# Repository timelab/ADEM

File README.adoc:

= Timelab ADEM project

image::https://api.travis-ci.org/timelab/ADEM.svg[alt="Build Status", link="https://travis-ci.org/timelab/ADEM", align="left", float]

The http://www.timelab.org/[Timelab] ADEM project enables cyclists to measure particulate matter (PM~1~ and PM~2.5~). The air quality estimate based on these measurements is displayed on the device, temporarily stored and sent via WiFi to a central data collection service.

The aim of this project is to create a low-cost open-source DIY hardware and firmware kit that is modular and adjustable, can be locally reproduced and repaired.

This git repository hosts the hardware designs, firmware and technical documentation for the ADEM device. You can find the documentation at: https://github.com/timelab/ADEM/tree/master/docs[]

More information related to this project is available from the project's wiki at: http://wiki.timelab.org/wiki/A.D.E.M[]

We welcome feedback and contributions.

image::http://timelab.github.io/ADEM-Logos/svg/adem_logo-txt_stroke.svg[alt="ADEM logo", link="http://ik-adem.be/", align="right", float]

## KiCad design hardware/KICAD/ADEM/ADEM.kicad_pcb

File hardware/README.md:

# Hardware

The project uses the SparkFun Thing. This ESP8266 based Wi-Fi controller development board runs the A.D.E.M. firmware and conveniently hosts a LiPo battery management system that is key in the mobility aspect of this project. Apart from the headers for the SparkFun Thing, the project's printed circuit board has room for a GPS module, temperature and pressure sensors and connections to external parts like the PPD40NS dust sensor.

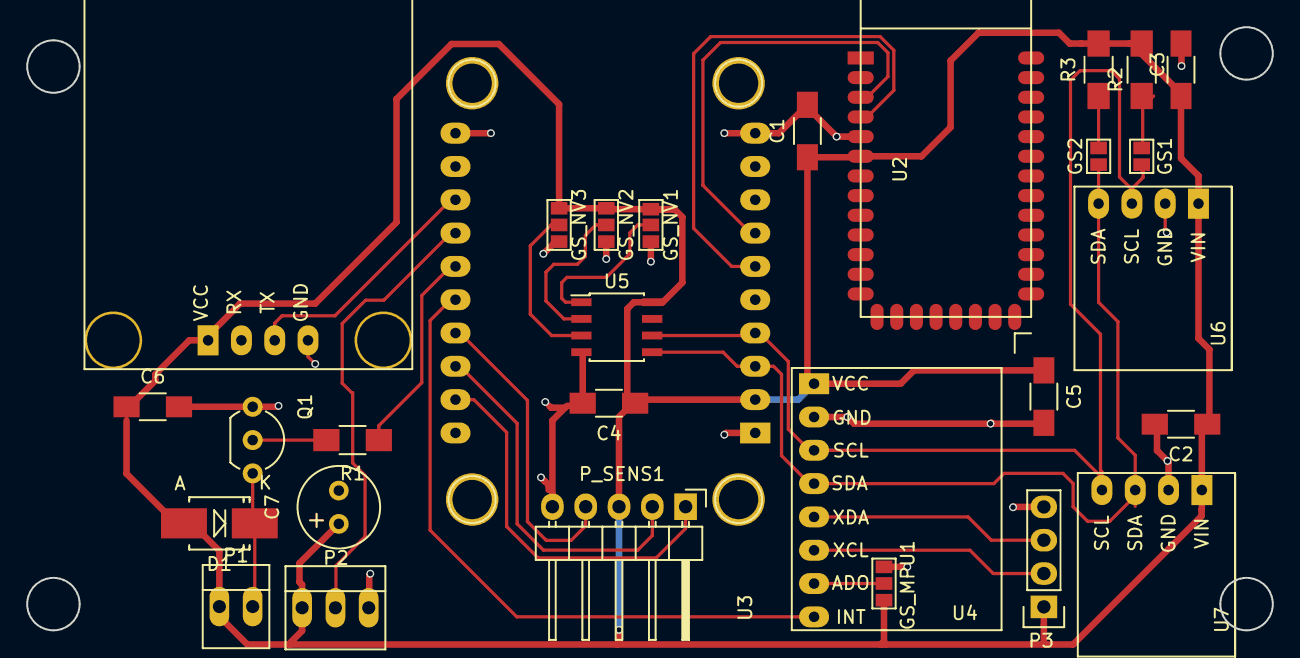
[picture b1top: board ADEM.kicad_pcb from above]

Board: 2 copper layers, 95.0 x 46.0 mm, 29 parts (0 on the bottom side), 23 nets.

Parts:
C1, C2, C3, C4, C5, C6: C; C_1206_HandSoldering
C7: CP; Elko_vert_11.2x6.3mm_RM2.5
D1: DIODE; SMB_Handsoldering
GS1: GS1; GS2
GS2: GS2
GS_MPU1: GS_A0; GS3
GS_NV1: GS_A0; GS3
GS_NV2: GS_A1; GS3
GS_NV3: GS_A2; GS3
P1: CONN_buzz; PINHEAD1-2
P2: CONN_01X03; PINHEAD1-3
P3: CONN_01X04; Pin_Header_Straight_1x04
P_SENS1: CONN_01X05; Pin_Header_Angled_1x05
Q1: NPN; TO-92_Inline_Wide
R1, R2, R3: R; R_1206_HandSoldering
U1: GY-NEO6MV2
U2: HC05; HC-05
U3: ESP8266_THING
U4: MPU6050
U5: NVSRAM; SOIC-8_3.9x4.9mm_Pitch1.27mm
U6: BMP180
U7: HTU21D

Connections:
A_SENSOR: P_SENS1.1, U3.19
BT_RX: U2.4, U3.6
BT_TX: U2.3, U3.7
BUZZ: R1.1, U3.15
GND: C1.2, C2.2, C3.2, C4.2, C5.2, C6.2, C7.2, GS_MPU1.3, GS_NV1.3, GS_NV2.3, GS_NV3.3, P2.3, P3.4, P_SENS1.5, Q1.1, U1.4, U2.5, U3.1, U3.10, U3.11, U4.2, U5.4, U6.2, U7.2
GPS_RX: U1.3, U3.13
INT: U3.16, U4.8
NEO_PXL: P2.2, U3.14
unnamed: D1.1, P1.2, Q1.3
unnamed: GS1.1, R2.2
unnamed: GS2.2, R3.1
unnamed: GS_MPU1.2, U4.7
unnamed: GS_NV1.2, U5.1
unnamed: GS_NV2.2, U5.2
unnamed: GS_NV3.2, U5.3
unnamed: P3.2, U4.6
unnamed: P3.3, U4.5
unnamed: Q1.2, R1.2
P10_SENS: P_SENS1.2, U3.18
P25_SENS: P_SENS1.4, U3.17
SCL: GS1.2, U3.4, U4.3, U5.6, U6.3, U7.4
SDA: GS2.1, U3.3, U4.4, U5.5, U6.4, U7.3
VCC: C1.1, C2.1, C3.1, C4.1, C5.1, C6.1, C7.1, D1.2, GS_MPU1.1, GS_NV1.1, GS_NV2.1, GS_NV3.1, P1.1, P2.1, P3.1, P_SENS1.3, R2.1, R3.2, U1.1, U2.6, U3.2, U4.1, U5.8, U6.1, U7.1

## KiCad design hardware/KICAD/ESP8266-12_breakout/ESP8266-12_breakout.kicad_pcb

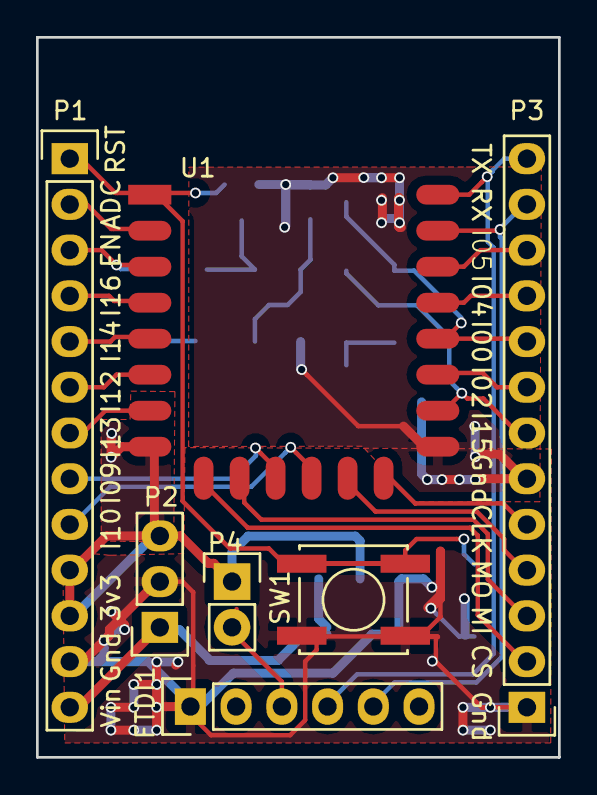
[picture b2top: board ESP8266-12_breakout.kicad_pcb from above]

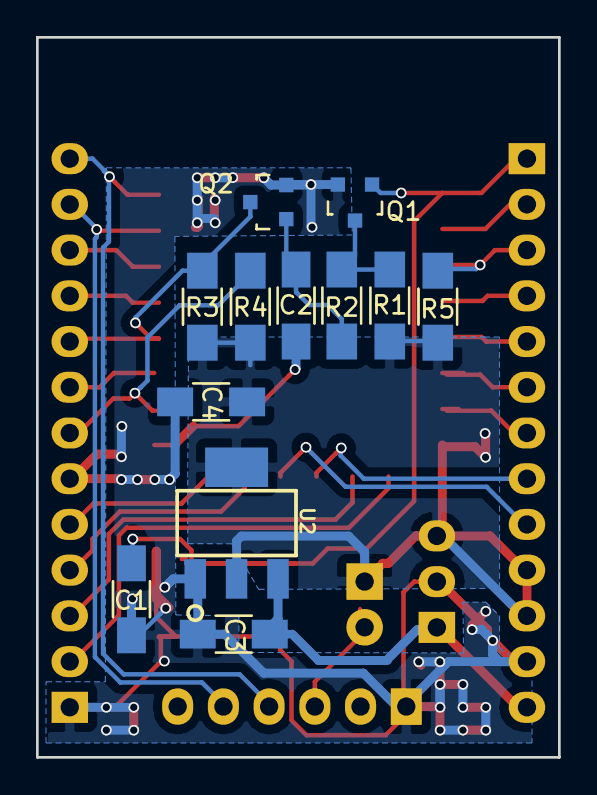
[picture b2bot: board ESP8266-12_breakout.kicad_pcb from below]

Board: 2 copper layers, 29.0 x 40.0 mm, 19 parts (12 on the bottom side), 26 nets.

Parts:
C1: 0.1 u; C_1206_HandSoldering
C2: 2u2; C_1206_HandSoldering
C3, C4: 10u; C_1206_HandSoldering
FTDI1: CONN_01X06; Pin_Header_Straight_1x06
P1, P3: CONN_01X13; Pin_Header_Straight_1x13
P2: CONN_01X03; Pin_Header_Straight_1x03
P4: CONN_01X02; Pin_Header_Straight_1x02
Q1, Q2: BSS138; SOT-23
R1: 470K; R_1206_HandSoldering
R2: 100K; R_1206_HandSoldering
R3, R4, R5: 10K; R_1206_HandSoldering
SW1: SW_PUSH; SW_SPST_EVPBF
U1: ESP-12E
U2: AP1117; SOT223

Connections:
+3V3: C4.1, P1.10, P1.11, P2.3, P4.1, R1.1, R3.1, R4.1, R5.1, U1.8, U2.0, U2.2
/ADC: P1.2, U1.2
/CS0: P3.2, U1.9
/ENA: P1.3, R5.2, U1.3
/GPIO00: P3.9, Q2.3, R3.2, U1.18
/GPIO02: P3.8, U1.17
/GPIO04: P3.10, U1.19
/GPIO05: P3.11, U1.20
/GPIO9: P1.8, U1.11
/GPIO10: P1.9, U1.12
/GPIO12: P1.6, U1.6
/GPIO13: P1.7, U1.7
/GPIO14: P1.5, U1.5
/GPIO15: P3.7, R4.2, U1.16
/GPIO16: P1.4, U1.4
/MISO: P3.3, U1.10
/MOSI: P3.4, U1.13
/RST: C1.1, P1.1, Q1.1, SW1.2, U1.1
/RX: FTDI1.5, P3.12, U1.21
/SCLK: P3.5, U1.14
/TX: FTDI1.4, P3.13, U1.22
/Vin: C3.1, P1.13, P2.1, U2.3
GND: C1.2, C2.2, C3.2, C4.2, FTDI1.1, P1.12, P2.2, P3.1, P3.6, Q1.2, Q2.2, SW1.1, U1.15, U2.1
unnamed: C2.1, Q2.1, R2.1
unnamed: FTDI1.3, P4.2
unnamed: Q1.3, R1.2, R2.2

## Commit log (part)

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2016-04-10 Documentation updates
2016-04-10 One more update
2016-04-10 Move MyAdem code to its own directory (Sketch complained)
2016-04-10 Adding another project to test Travis CI compilation
2016-04-10 Move kavers1's best example in place
2016-04-10 More components become part of an upcoming alpha release
2016-04-10 Move docs around, document .travis.yml
2016-04-10 Add report function to Ppd42
2016-04-10 Remove duplicate include of Wire.h
2016-04-11 GitHub cannot align images in AsciiDoc, changing the approach
2016-04-13 Added sketches i've been experimenting with
2016-04-13 Ignore every config.h file (for all sketches)
2016-04-13 Add logo to documentation
2016-04-13 Rename internal libraries according to new naming convention
2016-04-13 Modify existing code using the new pin assignments and library code
2016-04-13 Use default boot mode baudrate (74880 baud)
2016-04-13 Indicate the project page and wiki are in Dutch only
2016-04-13 Add question and answers section
2016-04-14 Improve styling by using titles for questions
2016-04-14 Add Q&A tothe index
2016-04-14 Add logo to GitHub and test integration
2016-04-14 Added first draft of pseudo-code and diagram
2016-04-14 Another test
2016-04-14 Small cosmetic change
2016-04-14 Added Lieven for the (in-memory) datastore library
2016-04-14 Ignore specific backup files
2016-04-14 Missing file from commit
2016-04-14 corrected _activated
2016-04-14 Update pseudo code, diagram and add colors
2016-04-14 Add references to buzzer
2016-04-14 Add collaboration spaces
2016-04-15 Add colors to states
2016-04-15 Update with new code diagram
2016-04-15 Add buzzer + cleanup
2016-04-15 Small update
2016-04-15 Cosmetic changes to make output bearable
2016-04-15 Added the new led_NeoPixel library but disable the code (since it doesn't work)
2016-04-15 Another item off the TODO list
2016-04-15 Cosmetic changes
2016-04-15 Added preliminary GPS code, doesn't compile though
    The main adem.ino was updated, but with commented pieces for GPS.
2016-04-15 Small clarification, this is the Sparkfun Development board
2016-04-15 Update TODO
2016-04-15 Adding gps.ready support and cosmetic changes
2016-04-16 fixed use of SoftwareSerial and TinyGPSPlus libraries in SwSerialGPS library
2016-04-16 Added Makefile to build code and flash your device
2016-04-16 Ignore ./Arduino and ./Build directories
2016-04-16 Remove unused task, recreate them when they are actually used
2016-04-16 Nope, it broke the Travis CI build, sigh (hung indefinitely)
2016-04-16 Control LED from main loop (only one statement for all states)
2016-04-16 Fix the humidity/temperature output, and reindent
2016-04-16 Add DEBUG support, changed to DEBUG_SCHED for scheduler
2016-04-17 Added gps_test example code for testing gps_SwSerial
2016-04-17 Small improvements to Makefile
2016-04-17 Added DEBUG_GPS, and only set gps.read to true when location data is received
2016-04-17 Document the use of the Makefile and DEBUG mode when developing
2016-04-17 Add serial input in DEBUG mode for influencing the state machine
2016-04-17 Create and destroy tasks during state transition, add restart key "r" to DEBUG mode
2016-04-17 Runaway debug statement removed
2016-04-17 Remove leftover piece
2016-04-17 Add altitude and speed to sensor data output
2016-04-18 Fix spelling of "latitude"
2016-04-21 added suspend and enable to the tasks
2016-04-21 typo
2016-04-22 Ignore arduino15 symlink, update Makefile to support MacOSX
2016-04-22 Copy free license to all files, revert to using DEBUG_SCHED for scheduler
2016-04-22 Cosmetic changes, ensure START state has red LED
2016-04-22 Move serial output from main program to library
2016-04-22 Integrate battery library into main program
2016-04-23 Add battery test sketch
2016-04-23 Prefix states, added stub classes for accelerometer and buffer, add test wifiap code
2016-04-24 changed reporting to accomodate buffering and serialization. this is needed for store and forward functionality If it breaks the code --> roll back to previous version
2016-04-24 Add known issues to TODO
2016-05-07 Added references for I2C info on GPS to accommodate the UART->I2C hack
2016-05-07 Circular buffer to do store and forward Base Class will be overwritten by file or memory implementation
2016-05-08 fixed link to logo
2016-05-08 added buffer capability to the reporting
2016-05-11 changed: store_And_Forward.h to store_and_forward.h => gave compile error in OSX changed: include <..\..\Sensor\Sensor.h> to #include <../../Sensor/Sensor.h> => gave compile error in OSX
2016-05-11 Maybe fix the Travis build status ?
2016-06-15 Assorted changes
    - Remove the StubBuffer now that we have a real buffer
    - Add a 500ms delay in the sleep state
    - Disconnect WIFI to improve battery consumption
    - Move upload_task() creation/suspension to state transition
    - Added some hints that state machine transitioned into sleep state
    - Added the Chip ID in the WIFI AP SSID
2016-07-13 Updated library ArduinoJson to v5.6.2
2016-07-13 Fix ADEM logo cfr. @kavers1
2016-07-13 Remove SVG image, now part of ADEM-Logos repository
2016-07-14 Clean up work-around for Arduino v1.6.8 and older
2016-07-14 Small cleanup
2016-07-15 Initial support for WIFI
2016-08-18 added accelero_mpu6050 sensor library this is not final yet but functional
2016-08-20 Fix a small typo
2016-08-20 I2C-GPS example code
2016-08-20 conditionally removed SD-logging
2016-08-21 Fix SSID for AP mode
2016-08-21 Updated library ArduinoJson to v5.6.5
2016-08-30 updated pin assignments and I2C/Wire speed
2016-08-30 addes debug logging needs to be cleaned up later
2016-08-30 disable debug output
2016-08-31 moved quote in link commands after tilde
2016-09-01 Increase verbosity
2016-09-12 Rename CXX_FLAGS to CFLAGS
2016-09-12 Add first implementation of DEMO mode
2016-09-22 Demo mode (#17)
    - Enables WIFI_AP and WebServer
    - Includes hard-coded demo HTML/javascript (adem/demo.h)
    - Webserver exports sensor data to HTML page as JSON
2016-09-25 Implementation of a captive portal (#19) (#21)
    This commit implements the captive portal idea.
    When you associate with the WIFI AP, you will get a logon pop-up, which
    gets you directly to the ADEM info page. And if you continue, you will
    get forwarded to http://adem.local/ whatever URL your browser targets.
    This fixes #19
2016-09-25 Ensure Travis doesn't complain (#22)
    Not sure why it worked on my laptop without this thought.
2016-09-28 Updated Arduino to v1.6.12 (#23)
    * Ensure Travis doesn't complain
    * Updated Arduino to v1.6.12
2016-09-30 Use platformIO with ESP8266 in Travis (#24)
2016-10-01 Add a ppd42_test program (#25)
    Also make the PPD pins configurable during instantiation.
    And convert tabs to spaces (more consistent).
2016-10-07 Fake Android captive portal internet check (#26)
    - Also update TODO with latest status
2016-10-09 added extra debug output
2016-10-09 Fix uint32 overflow and DEBUG_PPD42 output (#27)
2016-10-09 Rename DEBUG to DEBUG_PPD42 (part 2) (#28)
2016-10-10 Use uint64_t for PPM information (#29)
    Also make ppd42_test easy to build for Arduino Uno
2016-10-10 Turn temperature into a float (#30)
2016-10-10 Add PM count and mass to DEMO page
    Web-page is a bit too complex, need @pecuchet to do this the right way(tm).
2016-10-10 Add PM count and mass to DEMO page (#32)
    Web-page is a bit too complex, need @pecuchet to do this the right way(tm).
2016-10-11 logging messages
2016-10-12 I2C gps arduino register redefine
2016-10-15 fixed date problem moved to seperate path
2016-10-15 try to fix travis
2016-10-15 forced add to overcome .ignore settings
2016-10-15 typo correction
2016-10-19 Add delay in demo-loop (improves WIFI stability)
2016-10-20 Learn Makefile to understand different HWTYPEs
    Since we now have 2 microcontrollers and 2 codebases for each
    respectively, we need to teach `make` which hardware is used for which
    project.
    - i2c-slave/i2c-slave.ino -> Arduino Pro Mini
    - everything else -> Sparkfun Thing
    But this can be overriden using eg. HWTYPE=uno
2016-10-20 Reorganize libraries, get rid of unwanted src/
2016-11-16 Rename PM10 consistently to PM1 to avoid confusion
2016-11-17 Fix the speed of the Arduino Pro Mini
2016-11-17 Reformatted codebase
    Functionally the same, but properly indented.
    Somewhat more debugging statements.
2016-11-17 Reformatted codebase (#41)
    Functionally the same, but properly indented.
    Somewhat more debugging statements.
2016-11-19 Changed PM25 to PM2.5 in the documentation
2016-11-20 corrected path in docs for new libraries location
2016-11-20 added instruction to exit monitor
2016-11-20 couple of documentation updates for Windows, estimate component power use
2016-11-20 (re)initialize I2CGps on read when initialization was not OK
2016-11-20 Restructured code, 100kHZ I2C
2016-11-20 stand alone I2C GPS program
2016-11-20 Small fix -- should wait for Travis before merging (#46)
    * Restructured code, 100kHZ I2C
    * Small fix -- should wait for Travis before merging
2016-12-10 Disable pullup on Arduino pro mini I2C (#47)
2017-01-25 adjusted word alignment in datastructure
    it seems that the ESP has a 32bit alignment in datastructure.
2017-01-25 adjust datastructure alignment to DWORD
2017-01-30 Added setClockStretchLimit for succesfull I2C communication
2017-01-31 I2C scanner update with neopixel
2017-01-31 ingnore visual studio files
2017-02-08 lowered baud rate for flashing to 460800 for better reliability
2017-02-09 added gps ready status. compiles but not tested yet
    wd_timestamp van 32 bit ipv 16 bit
    bij faling wdt wordt de dataset niet meer gereset naar 0 maar enkel de
    ready status vlag afgezet
2017-02-12 update status led blinks
    1 blink for general looping (detects hanging of arduino)
    2 blinks if gps fix is available
    3 blinks if gps fix and I2C communication
2017-03-08 startup fixes
2017-03-15 Lower baudrate for uploading firmware
2017-03-15 Revert the serial baudrate config
2017-04-14 wifimanager multi access point autoconnect
2017-04-20 remote debug capabilities
    Dit is een library die remote debug over telnet toelaat. Vermoedelijk
    hebben we die niet nodig in een final release
2017-04-20 add remote debugging
    added remote telnet debugging
2017-04-20 cleanup
2017-04-30 bug fixes in wifimanager and master ino
2017-05-02 store and forward fixes and sensor virtual reporting
2017-05-03 conditional debug output
2017-05-11 fixed ID problem for store and forward
2017-06-14 Added humidity sensor
2017-06-22 same serial baud rate as esp output
2017-06-26 I2C debugging
2017-11-22 moved demo.ino to its own folder
2017-11-24 added memory ID for I2C scanner
2017-11-24 test store and forward
2017-12-03 Move main project files back into adem/
2017-12-03 Add shippable config file for Arduino tests
2017-12-03 Remove demo code
2017-12-03 Ignore more (VSCode and PlatformIO) files by default
2017-12-03 Removed obsolete requirement for symlinks to libraries. Added instructions for forking, pushing and pull request.
2017-12-04 Clean up CI scripts
2017-12-04 Add both adem and i2c-gps projects in parallel (#62)
    * Clean up CI scripts
    * Add both adem and i2c-gps projects in parallel
    Testing if this works better.
    Now the adem and i2c-gps builds are in parallel.
2017-12-04 Remove leftover file (#63)
2017-12-04 Build i2c-slave for arduino mini pro
2017-12-04 Various small changes
    This PR includes:
    - Numbering fixes
    - Some formatting changes
    - And a typo fix
2017-12-06 buffered webserver
2017-12-06 renamed file
2017-12-06 Update .gitignore file
2018-08-01 Changed wording in the readme to air quality estimate New address of Timelab ESP32?
2018-09-03 Updated WiFiManager to v0.14
2019-03-30 fixed escaped qutoes
2019-05-11 no persenal info tracking
2019-05-11 Tel net wifi (#73)
    * test heap size and delete dynamic values in webserver
    * added html for redirection
    * fixed escaped qutoes
    * type cast
    * no persenal info tracking
    * typedasts
2019-05-26 type casting
2019-05-27 recreated the modification of #70
2019-05-27 exclude platformio .build
